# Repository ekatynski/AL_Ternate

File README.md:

# AL_Ternate Buffer
Simple DI buffer for recording purposes. The basic idea is one input, two outputs, 

## Requirements
- Able to accept a single mono or stereo signal at a high-impedance input (mono jack input will output on both channels)
- Have two identical outputs buffering the same mono or stereo signal to each output
- As the name implies, this device will have unity gain; this is a buffer, not an amplifier
- This device will be operable using a standard 9V battery inside the housing
- This device will be operable using a 9V (or higher - TBR) center-negative supply, diode-OR'd with the battery
- The buffer shall be of high enough bandwidth such that the buffered signal sounds identical to the original
- (TBR) This device shall be true bypass

## To Do
- [ ] Base-level schematic capture
- [ ] Layout

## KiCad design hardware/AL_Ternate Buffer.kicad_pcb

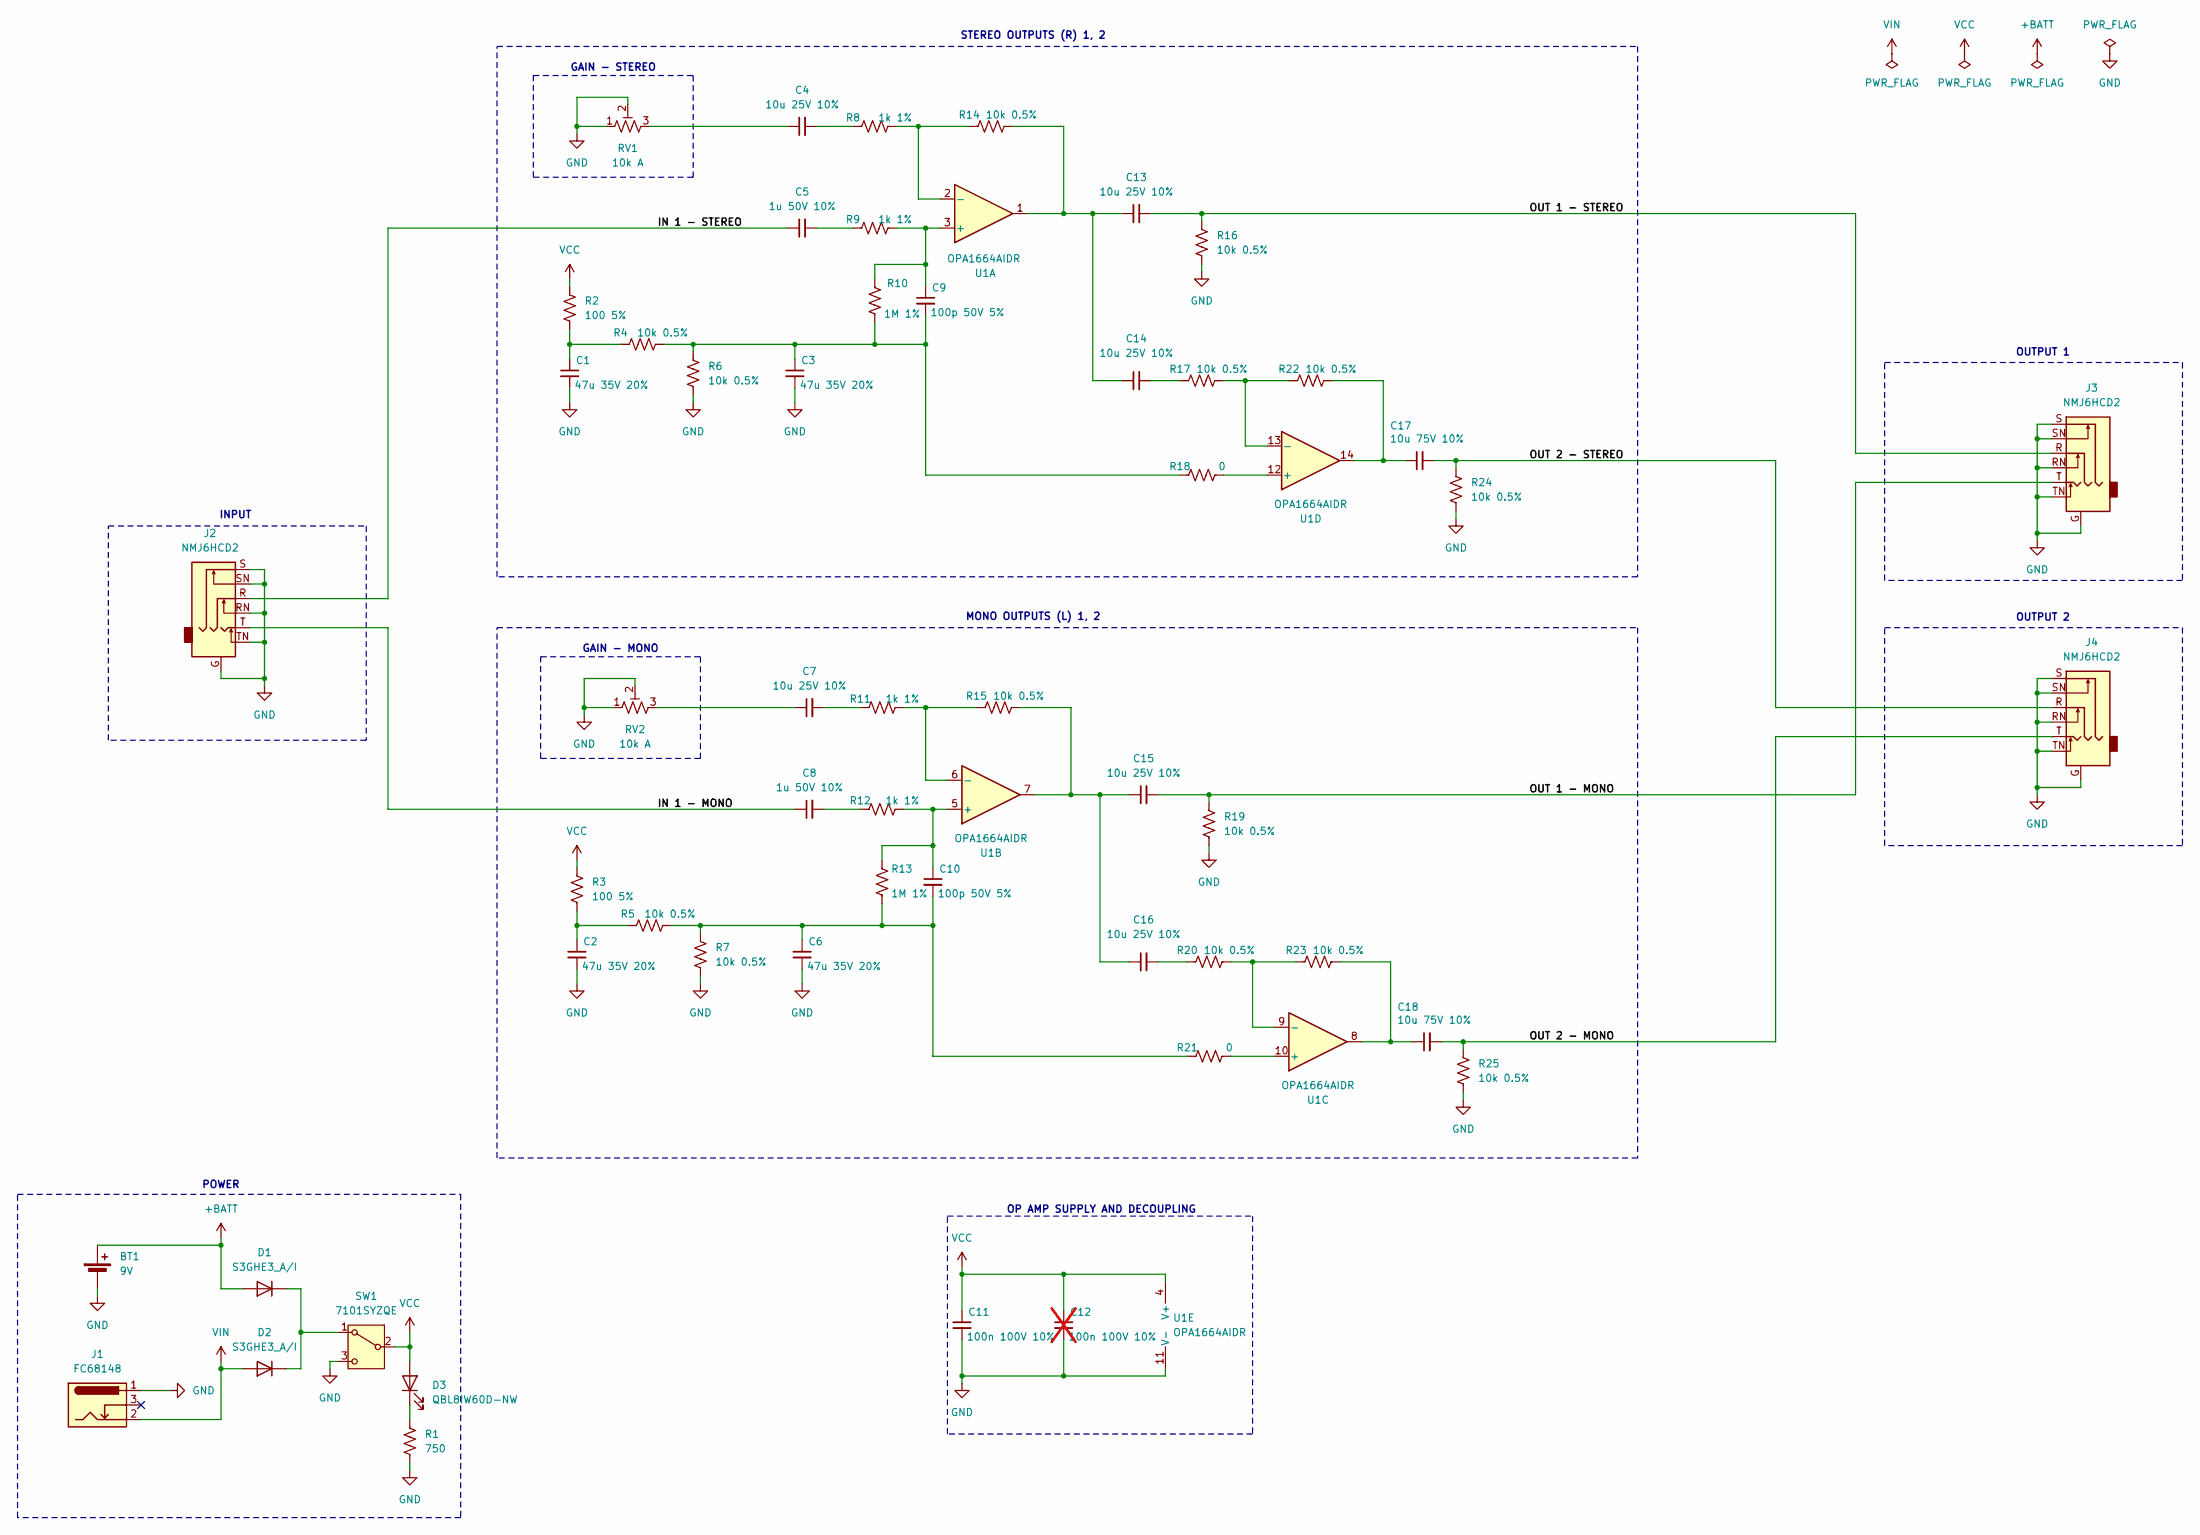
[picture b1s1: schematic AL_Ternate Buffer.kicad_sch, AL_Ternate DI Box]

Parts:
BT1: 9V; PinHeader_2x01_P2.54mm_Vertical; Part Number 232-M
C1, C2, C3, C6: 47u 35V 20%; C_2220_5750Metric_Pad1.97x5.40mm_HandSolder; Part Number CGA9N1X7R1V476M230KC
C4, C7, C13, C14, C15, C16: 10u 25V 10%; C_0805_2012Metric_Pad1.18x1.45mm_HandSolder; Part Number GRT21BC71E106KE13L
C5, C8: 1u 50V 10%; C_0805_2012Metric_Pad1.18x1.45mm_HandSolder; Part Number GCM21BR71H105KA03L
C9, C10: 100p 50V 5%; C_0805_2012Metric_Pad1.18x1.45mm_HandSolder; Part Number GCM2165C1H101JA16D
C11: 100n 100V 10%; C_0805_2012Metric_Pad1.18x1.45mm_HandSolder; Part Number GCJ21BR72A104KA01L
C12: 100n 100V 10%; C_0805_2012Metric_Pad1.18x1.45mm_HandSolder; Part Number GCJ21BR72A104KA01L; not fitted
C17, C18: 10u 75V 10%; C_1210_3225Metric_Pad1.33x2.70mm_HandSolder; Part Number CGA6P1X7R1N106K250AC
D1, D2: S3GHE3_A/I; D_SMB-SMC_Universal_Handsoldering; Part Number S3GHE3_A/I
D3: QBL8IW60D-NW; LED_D5.0mm; Part Number QBL8IW60D-NW
J1: FC68148; BarrelJack_Horizontal; Part Number FC68148
J2, J3, J4: NMJ6HCD2; Jack_6.35mm_Neutrik_NMJ6HCD2_Horizontal; Part Number NMJ6HCD2
R1: 750; R_0603_1608Metric_Pad0.98x0.95mm_HandSolder; Part Number 560112116101
R2, R3: 100 5%; R_0603_1608Metric_Pad0.98x0.95mm_HandSolder; Part Number RMCA0603JT100R-HP
R4, R5, R6, R7, R14, R15, R16, R17, R19, R20, R22, R23, R24, R25: 10k 0.5%; R_0603_1608Metric_Pad0.98x0.95mm_HandSolder; Part Number CRCW060310K0DKEAHP
R8, R9, R11, R12: 1k 1%; R_0603_1608Metric_Pad0.98x0.95mm_HandSolder; Part Number RCA06031K00FKEASR
R10, R13: 1M 1%; R_0603_1608Metric_Pad0.98x0.95mm_HandSolder; Part Number RCA06031M00FKEASR
R18, R21: 0; R_0603_1608Metric_Pad0.98x0.95mm_HandSolder; Part Number 560112116001
RV1, RV2: 10k A; Potentiometer_Runtron_RM-065_Vertical; Part Number PT6KV-103A2020
SW1: 7101SYZQE; PinHeader_1x03_P2.54mm_Vertical; Part Number 7101SYZQE
U1: OPA1664AIDR; SOIC-14_3.9x8.7mm_P1.27mm; Part Number OPA1664AIDR

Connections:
+BATT: BT1.1 (+), D1.2 (A)
/IN 1 - MONO: C8.1, J2.T
/IN 1 - STEREO: C5.1, J2.R
/OUT 1 - MONO: C15.2, J3.T, R19.1
/OUT 1 - STEREO: C13.2, J3.R, R16.1
/OUT 2 - MONO: C18.2, J4.T, R25.1
/OUT 2 - STEREO: C17.2, J4.R, R24.1
GND: BT1.2 (-), C1.2, C2.2, C3.2, C6.2, C11.2, C12.2, J1.1, J2.G, J2.RN, J2.S, J2.SN, J2.TN, J3.G, J3.RN, J3.S, J3.SN, J3.TN, J4.G, J4.RN, J4.S, J4.SN, J4.TN, R1.2, R6.2, R7.2, R16.2, R19.2, R24.2, R25.2, RV1.1, RV1.2, RV2.1, RV2.2, SW1.3 (C), U1.11 (V-)
unnamed: C1.1, R2.2, R4.1
unnamed: C2.1, R3.2, R5.1
unnamed: C3.1, C9.2, R4.2, R6.1, R10.2, R18.1
unnamed: C4.1, RV1.3
unnamed: C4.2, R8.1
unnamed: C5.2, R9.1
unnamed: C7.1, RV2.3
unnamed: C7.2, R11.1
unnamed: C8.2, R12.1
unnamed: C6.1, C10.2, R5.2, R7.1, R13.2, R21.1
unnamed: C13.1, C14.1, R14.2, U1.1
unnamed: C14.2, R17.1
unnamed: C15.1, C16.1, R15.2, U1.7
unnamed: C16.2, R20.1
unnamed: C17.1, R22.2, U1.14
unnamed: C18.1, R23.2, U1.8
unnamed: D1.1 (K), D2.1 (K), SW1.1 (A)
unnamed: D3.1 (K), R1.1
unnamed: C9.1, R9.2, R10.1, U1.3 (+)
unnamed: R8.2, R14.1, U1.2 (-)
unnamed: C10.1, R12.2, R13.1, U1.5 (+)
unnamed: R11.2, R15.1, U1.6 (-)
unnamed: R21.2, U1.10 (+)
unnamed: R20.2, R23.1, U1.9 (-)
unnamed: R18.2, U1.12 (+)
unnamed: R17.2, R22.1, U1.13 (-)
VCC: C11.1, C12.1, D3.2 (A), R2.1, R3.1, SW1.2 (B), U1.4 (V+)
VIN: D2.2 (A), J1.2

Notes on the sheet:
GAIN - MONO
GAIN - STEREO
INPUT
STEREO OUTPUTS (R) 1, 2
OP AMP SUPPLY AND DECOUPLING
POWER
OUTPUT 1
OUTPUT 2
MONO OUTPUTS (L) 1, 2

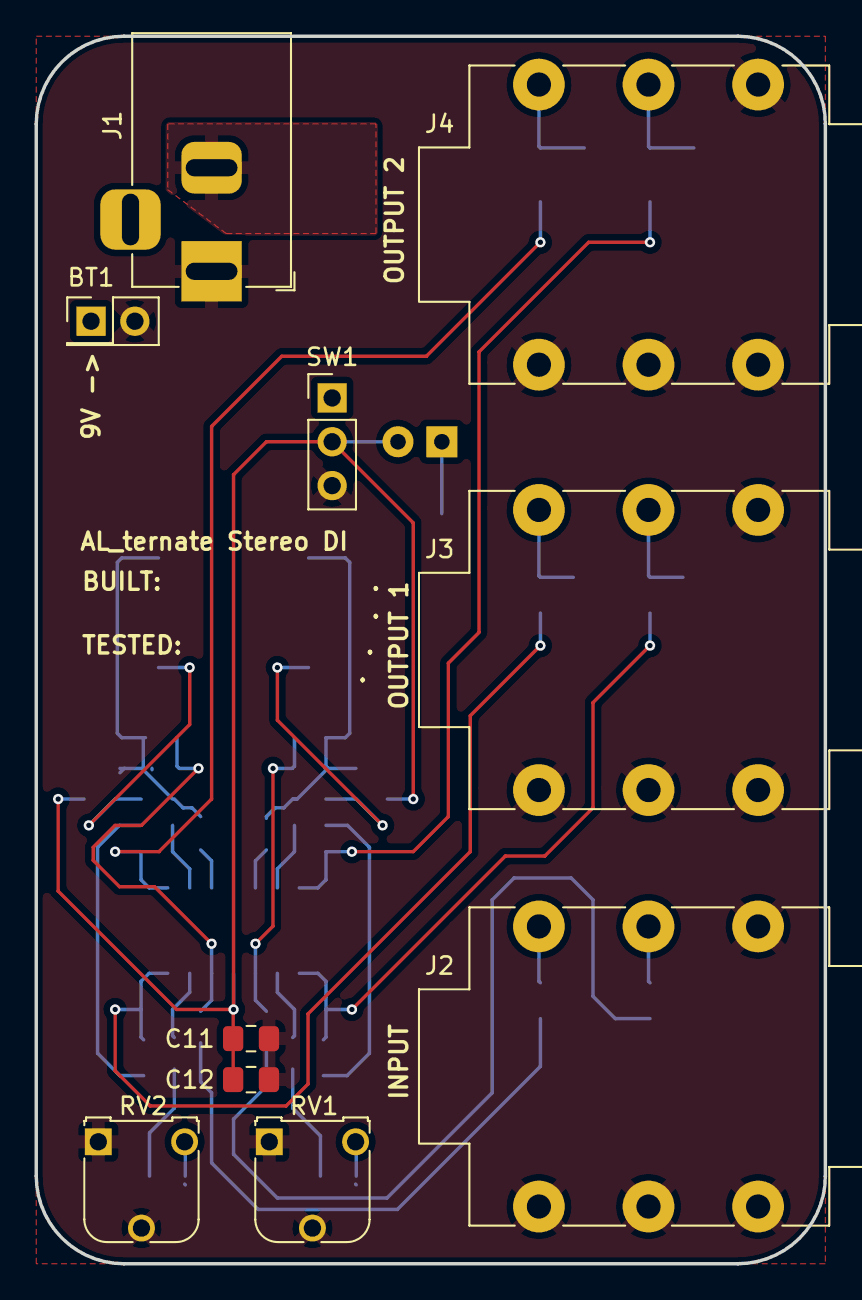
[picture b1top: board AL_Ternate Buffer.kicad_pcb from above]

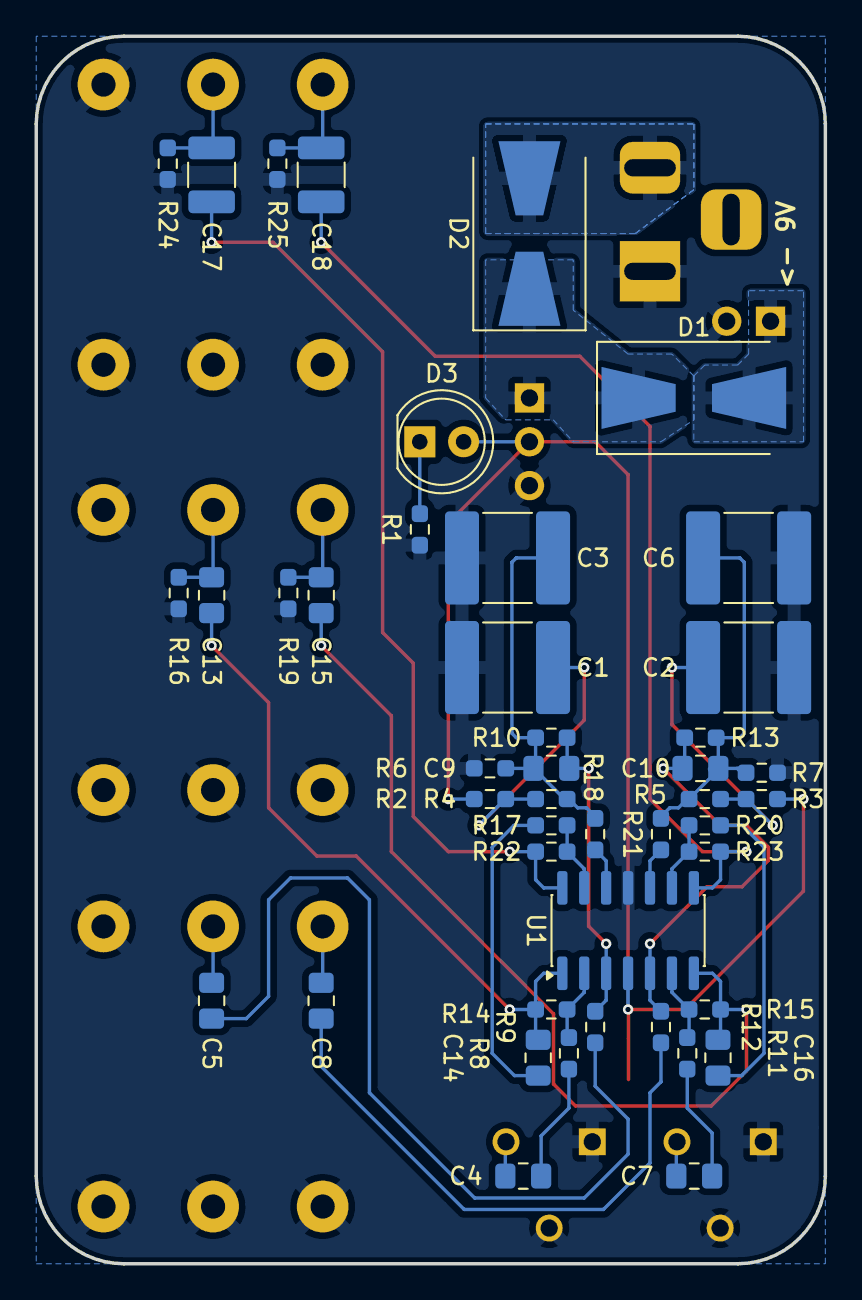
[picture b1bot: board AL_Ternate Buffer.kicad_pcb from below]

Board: 2 copper layers, 45.7 x 71.1 mm, 55 parts (45 on the bottom side), 36 nets.

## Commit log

2026-05-31 Added .gitignore file.
2026-05-31 README update.
2026-05-31 Added lib and ref directories.
2026-05-31 Project init.
2026-05-31 Backlink to CADLAB.io has been added.
2026-05-31 Added reference image.
2026-05-31 Very baseline schematic additions.
2026-06-01 Added schematic title block details.
2026-06-06 Cursory schematic capture, awaiting proper part selections.
2026-06-06 Power LED added.
2026-06-06 Gave up on pretentious switching jack Chassis setup, it's Ground or nothing now.
2026-06-06 Template PCB setup.
2026-06-06 Tentative schematic finish.
2026-06-06 PCB sheet setup.
2026-06-06 Cursory start to layout.
2026-06-06 Loose component grouping.
2026-06-07 Caught error regarding op-amp polarity. Partial routing/placement progress.
2026-06-07 Added 3D models for components lacking.
2026-06-11 Further routing.
2026-06-15 Finished tentative routing.
